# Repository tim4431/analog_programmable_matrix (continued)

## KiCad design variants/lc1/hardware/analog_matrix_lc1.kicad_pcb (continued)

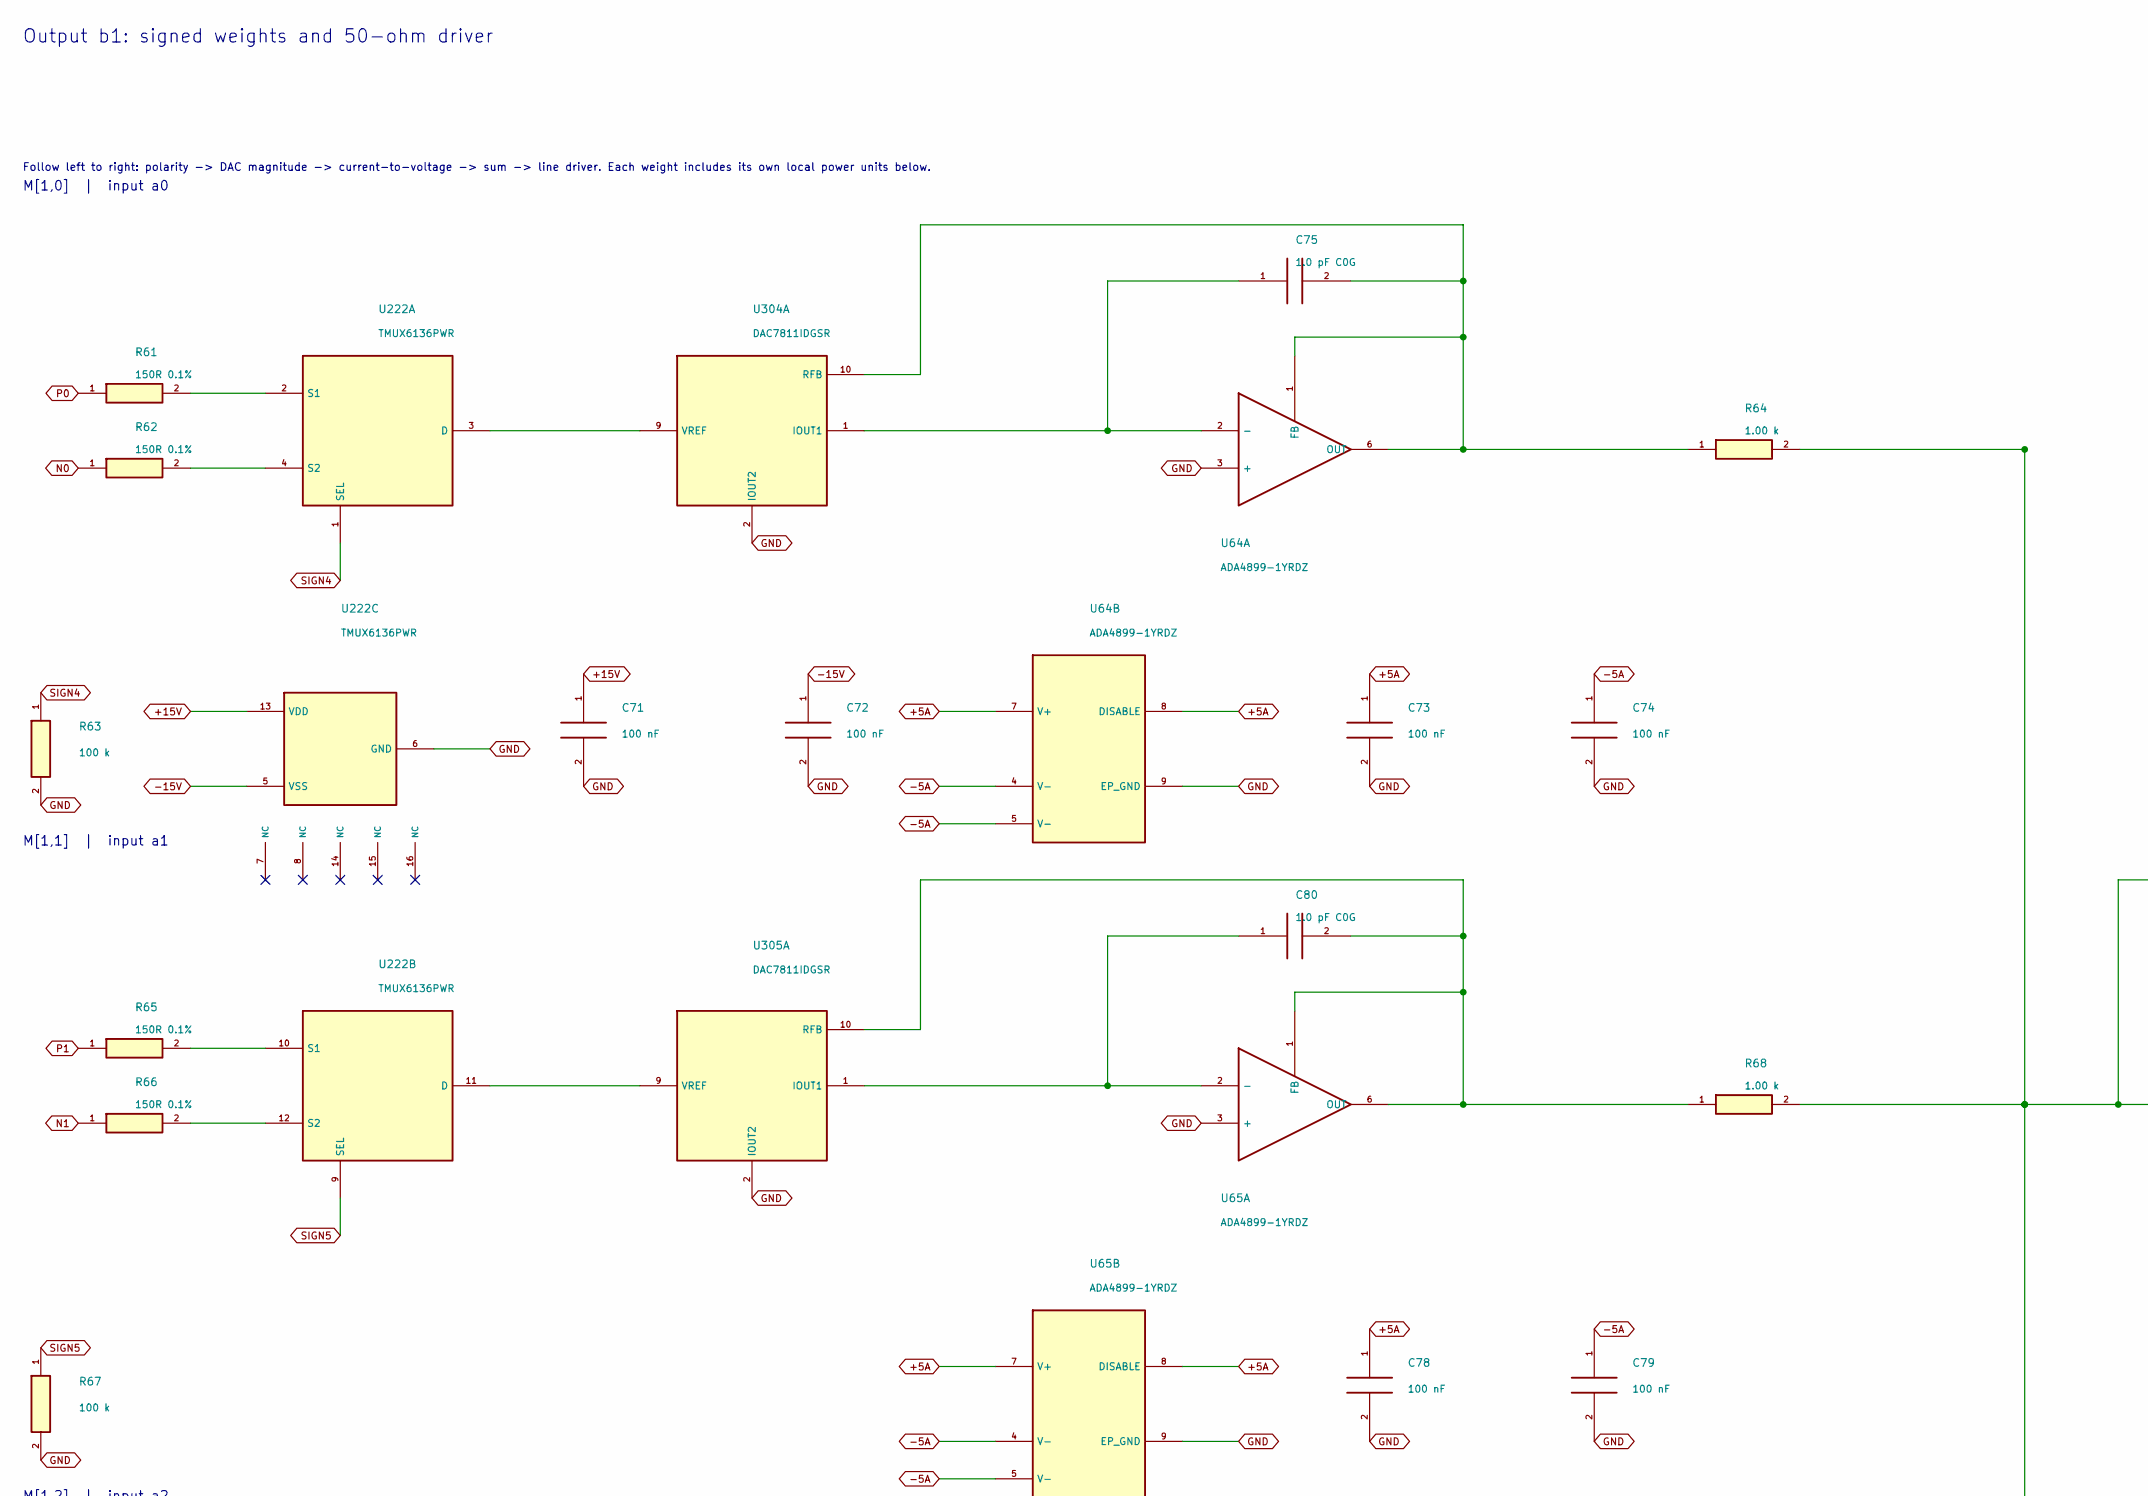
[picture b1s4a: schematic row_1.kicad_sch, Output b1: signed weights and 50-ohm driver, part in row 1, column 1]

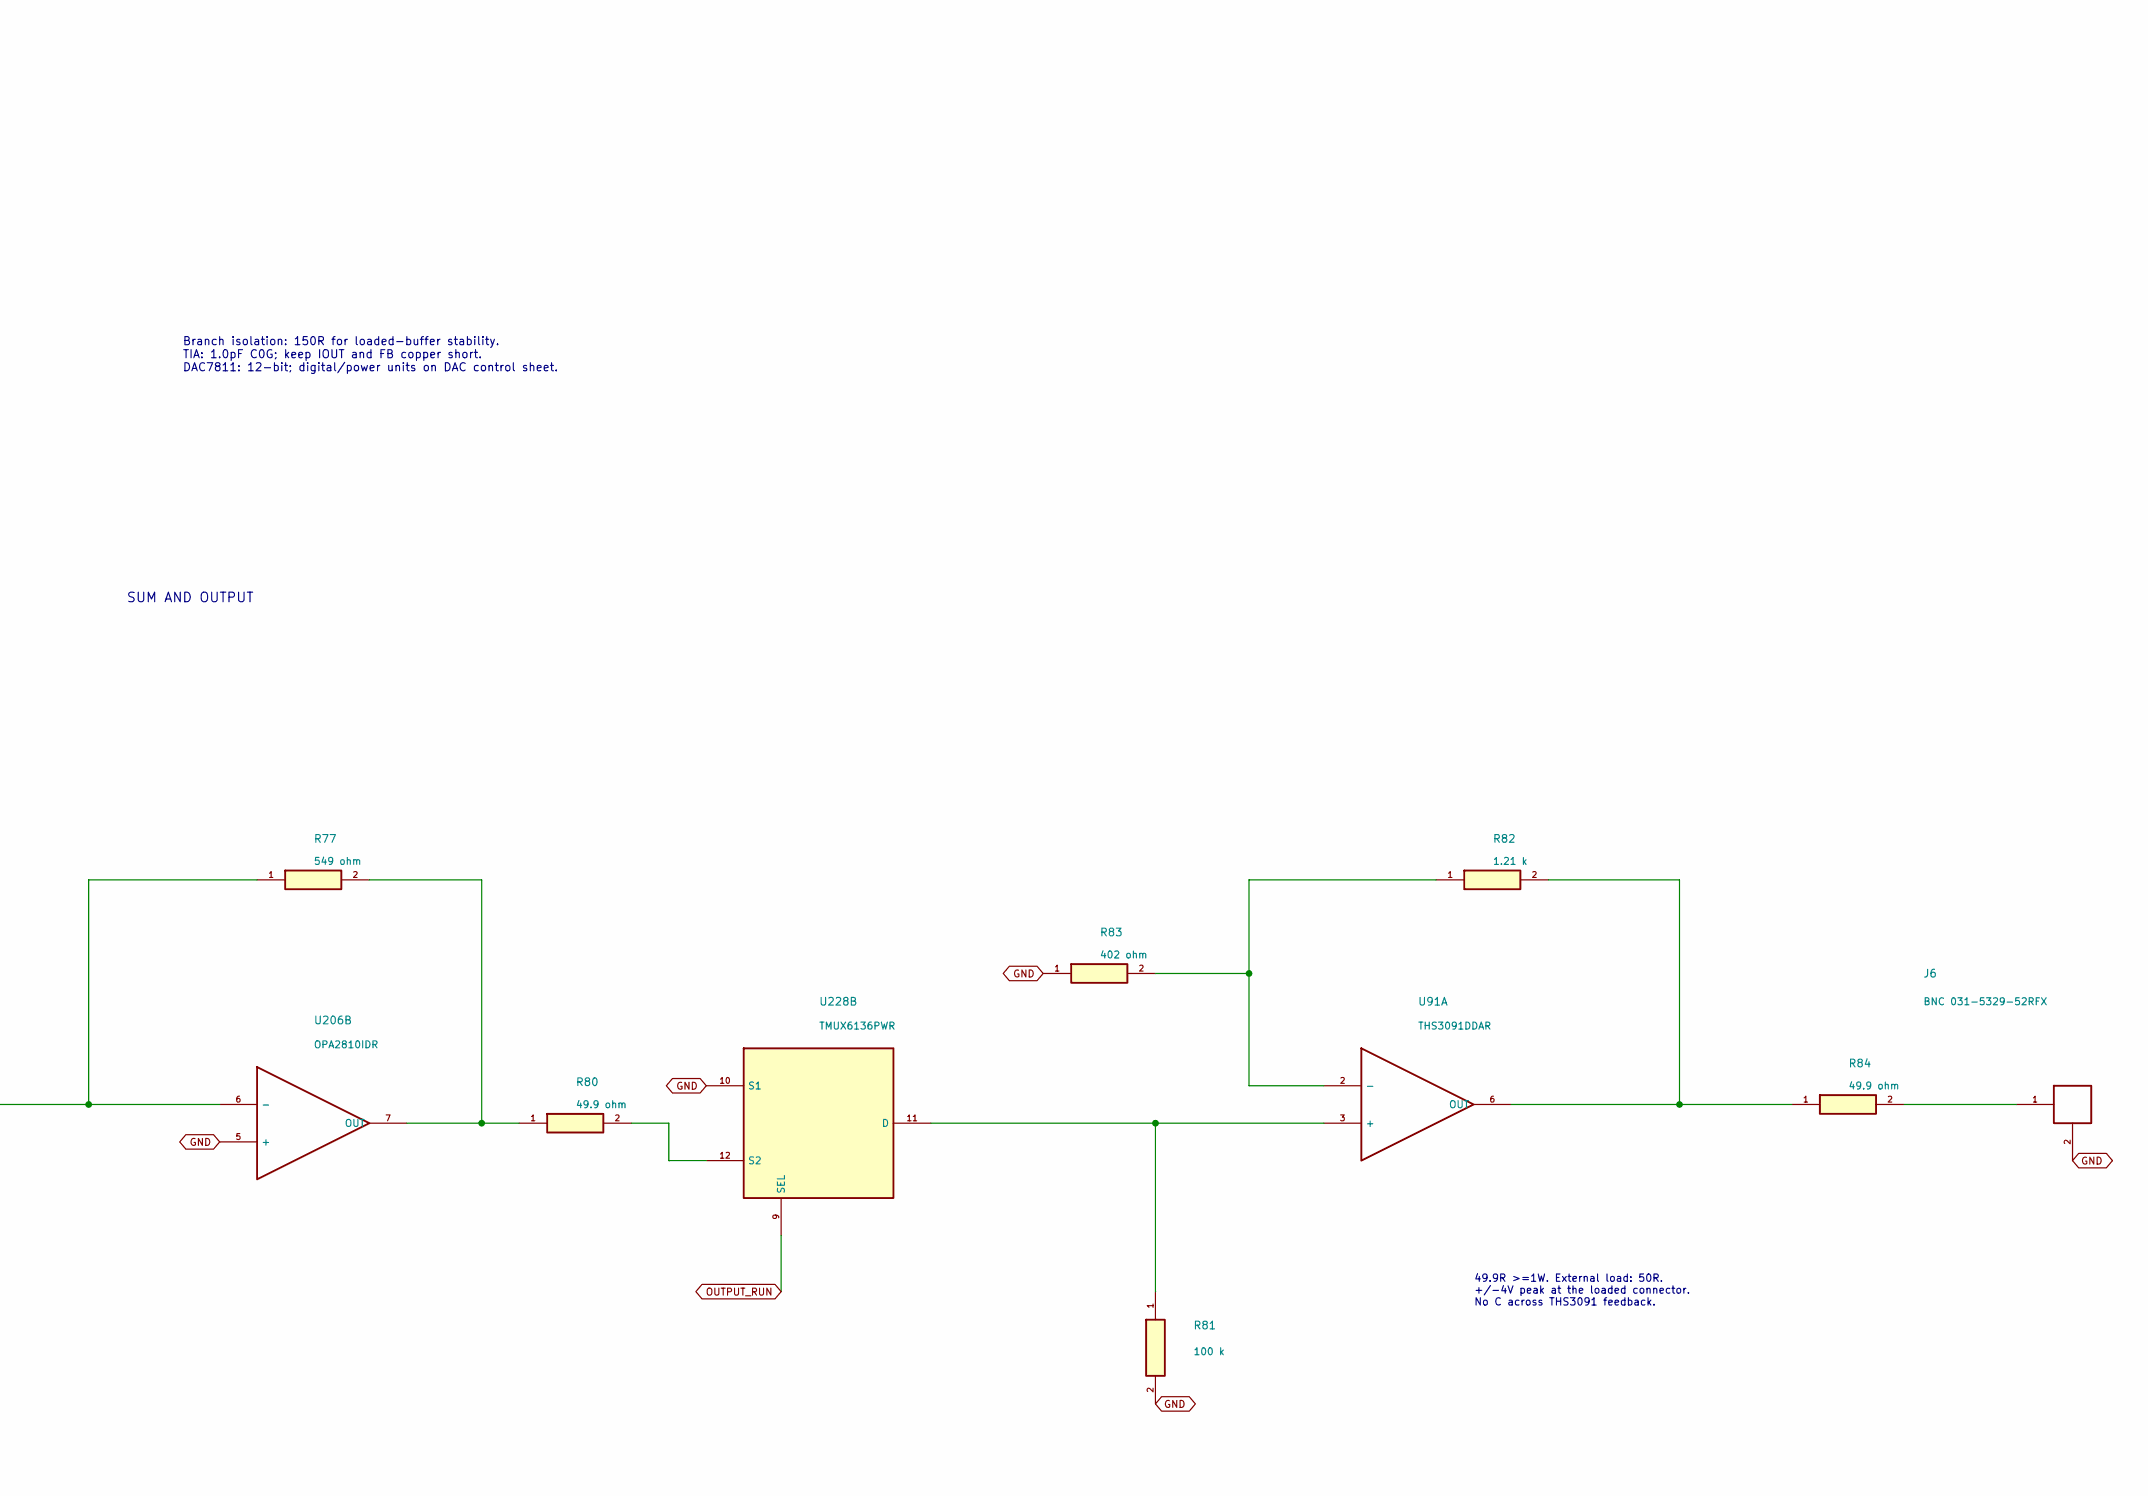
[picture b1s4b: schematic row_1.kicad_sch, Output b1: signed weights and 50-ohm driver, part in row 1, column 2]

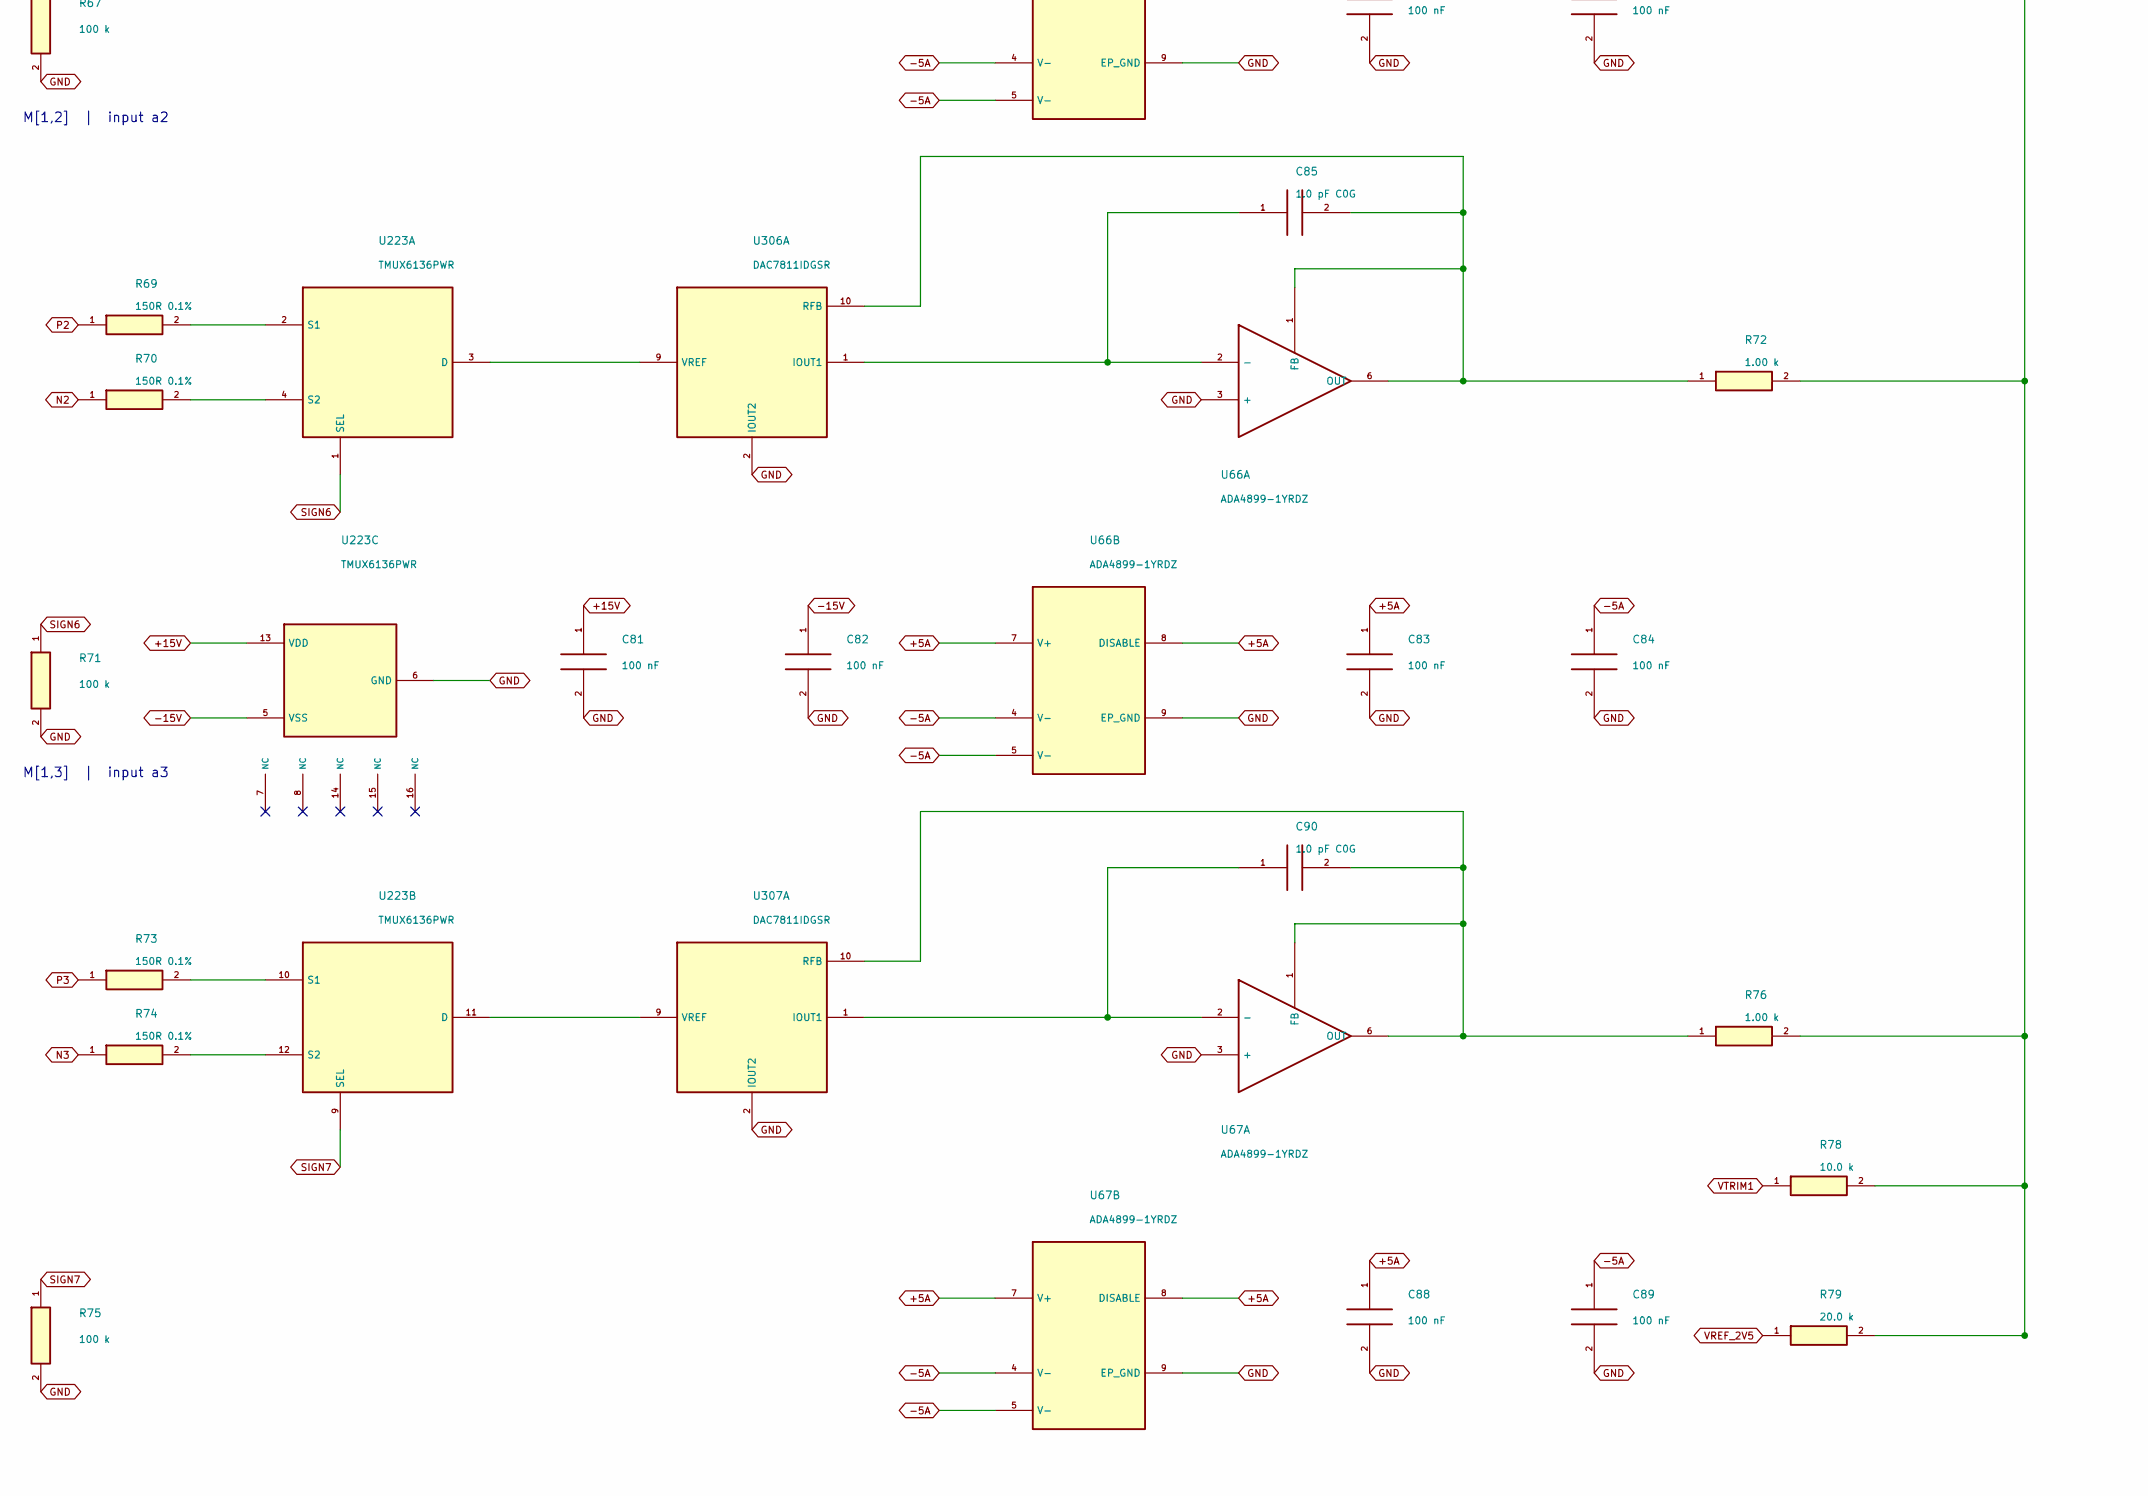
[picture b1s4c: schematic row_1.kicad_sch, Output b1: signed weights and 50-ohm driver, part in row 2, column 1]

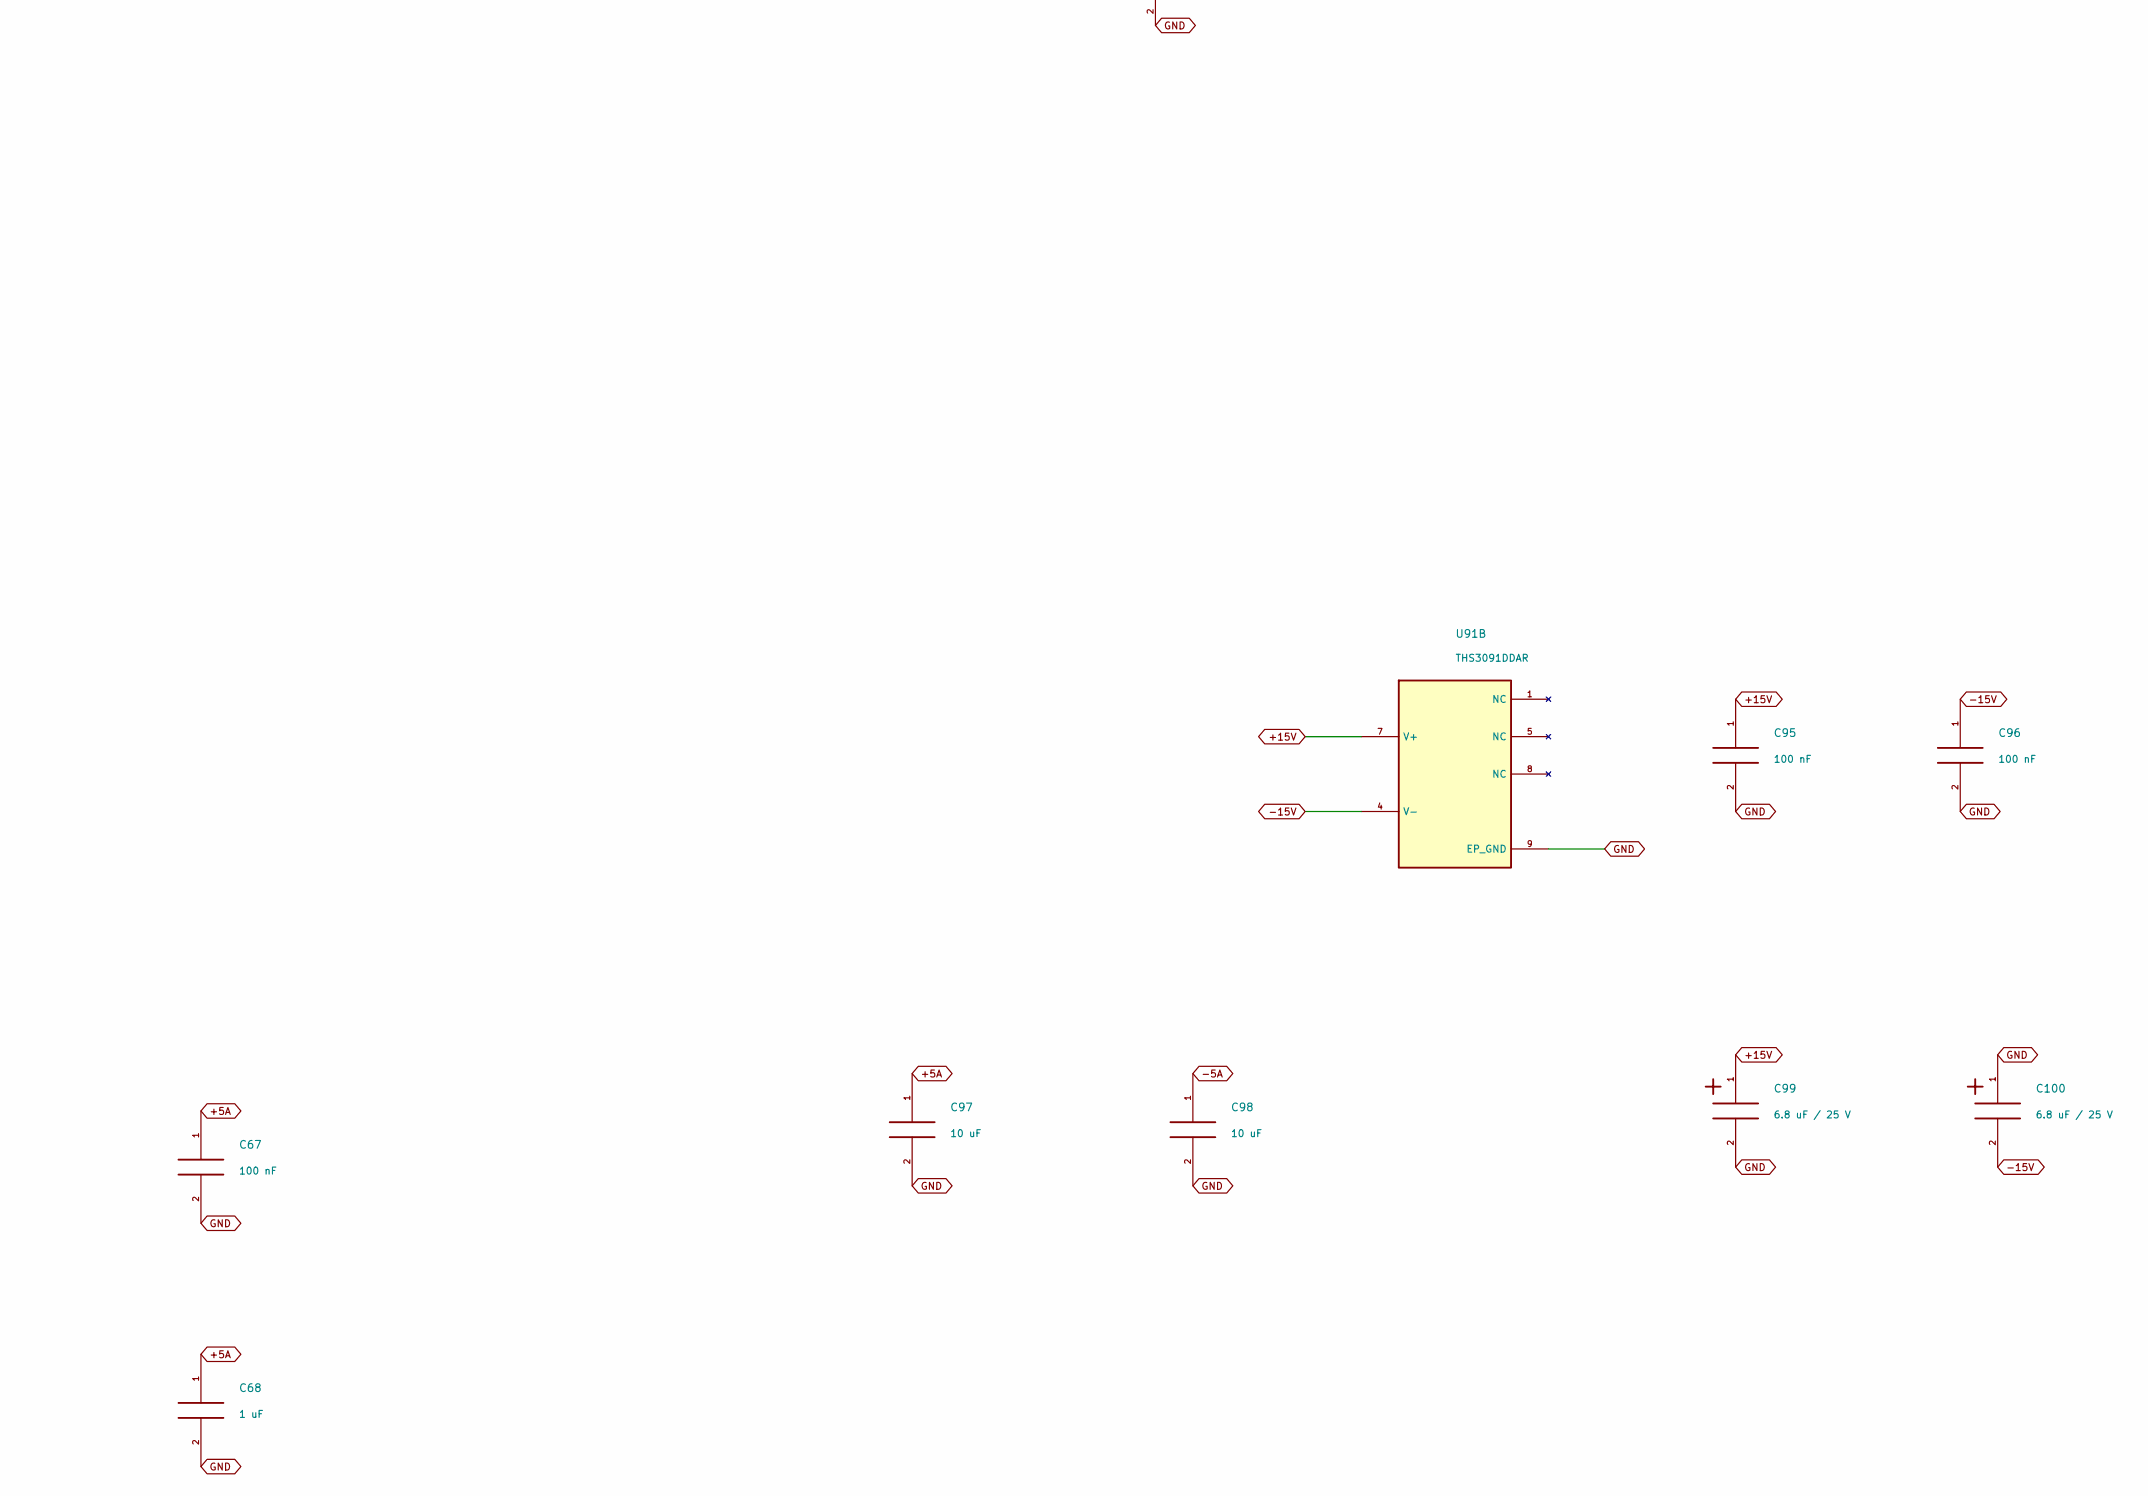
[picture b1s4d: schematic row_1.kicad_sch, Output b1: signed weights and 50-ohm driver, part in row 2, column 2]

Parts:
C67, C71, C72, C73, C74, C78, C79, C81, C82, C83, C84, C88, C89, C95, C96: 100 nF; C_0603_1608Metric; Rating 25V X7R minimum; effective C after bias
C68: 1 uF; C_0805_2012Metric; Rating 25V X7R minimum; effective C after bias
C75, C80, C85, C90: 1.0 pF C0G; C_0402_1005Metric; Rating 50V C0G, +/-0.1pF; stray capacitance in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
C97, C98: 10 uF; C_0805_2012Metric; Rating 25V X7R minimum; effective C after bias
C99, C100: 6.8 uF / 25 V; CP_EIA-3216-18_Kemet-A; Rating 25V polarized
J6: BNC 031-5329-52RFX; BNC_Amphenol_031-5329-52RFX_Vertical
R61, R62, R65, R66, R69, R70, R73, R74: 150R 0.1%; R_0603_1608Metric; Rating 0.1%, <=25ppm/C; 0.1W minimum
R63, R67, R71, R75, R81: 100 k; R_0603_1608Metric; Rating 0.1%, <=25ppm/C; 0.1W minimum
R64, R68, R72, R76: 1.00 k; R_0603_1608Metric; Rating 0.1%, <=25ppm/C; 0.1W minimum
R77: 549 ohm; R_0603_1608Metric; Rating 0.1%, <=25ppm/C; 0.1W minimum
R78: 10.0 k; R_0603_1608Metric; Rating 0.1%, <=25ppm/C; 0.1W minimum
R79: 20.0 k; R_0603_1608Metric; Rating 0.1%, <=25ppm/C; 0.1W minimum
R80: 49.9 ohm; R_0603_1608Metric; Rating 0.1%, <=25ppm/C; 0.1W minimum
R82: 1.21 k; R_0603_1608Metric; Rating 0.1%, <=25ppm/C; 0.1W minimum
R83: 402 ohm; R_0603_1608Metric; Rating 0.1%, <=25ppm/C; 0.1W minimum
R84: 49.9 ohm; R_2512_6332Metric; Rating 0.1%, <=25ppm/C; >=1W
U64, U65, U66, U67: ADA4899-1YRDZ; ADA4899_RD8_EP2.29x2.29
U91: THS3091DDAR; SOIC-8-1EP_3.9x4.9mm_P1.27mm_EP2.95x4.9mm_Mask2.71x3.4mm_Th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
U206: OPA2810IDR; SOIC-8_3.9x4.9mm_P1.27mm
U222, U223, U228: TMUX6136PWR; TSSOP-16_4.4x5mm_P0.65mm
U304, U305, U306, U307: DAC7811IDGSR; VSSOP-10_3x3mm_P0.5mm

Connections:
+5A: C67.1, C68.1, C73.1, C78.1, C83.1, C88.1, C97.1, U64.7 (V+), U64.8 (DISABLE), U65.7 (V+), U65.8 (DISABLE), U66.7 (V+), U66.8 (DISABLE), U67.7 (V+), U67.8 (DISABLE); also elsewhere on the board
+15V: C71.1, C81.1, C95.1, C99.1, U91.7 (V+), U222.13 (VDD), U223.13 (VDD); also elsewhere on the board
-5A: C74.1, C79.1, C84.1, C89.1, C98.1, U64.4 (V-), U64.5 (V-), U65.4 (V-), U65.5 (V-), U66.4 (V-), U66.5 (V-), U67.4 (V-), U67.5 (V-); also elsewhere on the board
-15V: C72.1, C82.1, C96.1, C100.2, U91.4 (V-), U222.5 (VSS), U223.5 (VSS); also elsewhere on the board
GND: C67.2, C68.2, C71.2, C72.2, C73.2, C74.2, C78.2, C79.2, C81.2, C82.2, C83.2, C84.2, C88.2, C89.2, C95.2, C96.2, C97.2, C98.2, C99.2, C100.1, J6.2, R63.2, R67.2, R71.2, R75.2, R81.2, R83.1, U64.3 (+), U64.9 (EP_GND), U65.3 (+), U65.9 (EP_GND), U66.3 (+), U66.9 (EP_GND), U67.3 (+), U67.9 (EP_GND), U91.9 (EP_GND), U206.5 (+), U222.6 (GND), U223.6 (GND), U228.10 (S1), U304.2 (IOUT2), U305.2 (IOUT2), U306.2 (IOUT2), U307.2 (IOUT2); also elsewhere on the board
N0: R62.1; also elsewhere on the board
N1: R66.1; also elsewhere on the board
N2: R70.1; also elsewhere on the board
N3: R74.1; also elsewhere on the board
unnamed: J6.1, R84.2
unnamed: R82.1, R83.2, U91.2 (-)
unnamed: R82.2, R84.1, U91.6 (OUT)
unnamed: R64.2, R68.2, R72.2, R76.2, R77.1, R78.2, R79.2, U206.6 (-)
unnamed: R77.2, R80.1, U206.7 (OUT)
unnamed: U222.3 (D), U304.9 (VREF)
unnamed: R61.2, U222.2 (S1)
unnamed: R62.2, U222.4 (S2)
unnamed: U222.11 (D), U305.9 (VREF)
unnamed: R65.2, U222.10 (S1)
unnamed: R66.2, U222.12 (S2)
unnamed: U223.3 (D), U306.9 (VREF)
unnamed: R69.2, U223.2 (S1)
unnamed: R70.2, U223.4 (S2)
unnamed: U223.11 (D), U307.9 (VREF)
unnamed: R73.2, U223.10 (S1)
unnamed: R74.2, U223.12 (S2)
unnamed: R81.1, U91.3 (+), U228.11 (D)
unnamed: R80.2, U228.12 (S2)
unnamed: C75.1, U64.2 (-), U304.1 (IOUT1)
unnamed: C75.2, R64.1, U64.1 (FB), U64.6 (OUT), U304.10 (RFB)
unnamed: C80.1, U65.2 (-), U305.1 (IOUT1)
unnamed: C80.2, R68.1, U65.1 (FB), U65.6 (OUT), U305.10 (RFB)
unnamed: C85.1, U66.2 (-), U306.1 (IOUT1)
unnamed: C85.2, R72.1, U66.1 (FB), U66.6 (OUT), U306.10 (RFB)
unnamed: C90.1, U67.2 (-), U307.1 (IOUT1)
unnamed: C90.2, R76.1, U67.1 (FB), U67.6 (OUT), U307.10 (RFB)
OUTPUT_RUN: U228.9 (SEL); also elsewhere on the board
P0: R61.1; also elsewhere on the board
P1: R65.1; also elsewhere on the board
P2: R69.1; also elsewhere on the board
P3: R73.1; also elsewhere on the board
SIGN4: R63.1, U222.1 (SEL); also elsewhere on the board
SIGN5: R67.1, U222.9 (SEL); also elsewhere on the board
SIGN6: R71.1, U223.1 (SEL); also elsewhere on the board
SIGN7: R75.1, U223.9 (SEL); also elsewhere on the board
VREF_2V5: R79.1; also elsewhere on the board
VTRIM1: R78.1; also elsewhere on the board

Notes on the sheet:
Output b1: signed weights and 50-ohm driver
Follow left to right: polarity -> DAC magnitude -> current-to-voltage -> sum -> line driver. Each weight includes its own local power units below.
M[1,0] | input a0
M[1,1] | input a1
M[1,2] | input a2
M[1,3] | input a3
SUM AND OUTPUT
49.9R >=1W. External load: 50R. +/-4V peak at the loaded connector. No C across THS3091 feedback.
Branch isolation: 150R for loaded-buffer stability. TIA: 1.0pF C0G; keep IOUT and FB copper short. DAC7811: 12-bit; digital/power units on DAC control sheet.
